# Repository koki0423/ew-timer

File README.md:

# timer

Arduino Nano を用いた 4 桁 7 セグメント表示付きタイマーの KiCad プロジェクトです。4 個の 4 ビット DIP スイッチで 16 ビットの設定値を入力し、開始/停止・リセット用の押しボタンで操作します。

このリポジトリには基板設計と製造データを収録しています。Arduino 用ファームウェア（`.ino` など）は含まれていません。

## 主な構成

| ブロック | 部品 | 役割 |
| --- | --- | --- |
| 制御 | A2: Arduino Nano v3.x | タイマー処理、表示走査、入力読取り |
| 表示 | U1: OSL-40391-LX | 4 桁・コモンカソードの 7 セグメント LED 表示器（コロン付き） |
| 表示駆動 | U2: 74HC595、R1-R8: 1 kΩ | シリアル出力を 8 本のセグメント信号（A-G、DP）へ展開。R1-R8 は各セグメントの電流制限抵抗 |
| 設定入力 | SW3-SW6: A7D-206-1、U3/U4: 74HC165、RN1-RN4: 10 kΩ | 4 個の 4 ビット DIP スイッチを 2 個の PISO シフトレジスタ経由で読み取る。各入力はプルダウンされ、スイッチ ON 時に High となる |
| 操作 | SW1、SW2 | リセット、開始/停止入力 |
| 状態表示 | U5: 74HC00、D1、R9: 300 Ω | DIP スイッチの一部を NAND 論理で判定し、エラー LED を点灯 |
| 電源安定化 | C1-C4: 0.1 µF | +5 V-GND 間のデカップリング |

基板外形は **120 mm × 90 mm**、板厚は **1.6 mm** です。表裏 2 層の配線を使用しています。

## Arduino Nano の接続

ファームウェアを作成する際は、以下の回路接続に合わせてピンを設定してください。

| Nano ピン | 接続先 | 用途 |
| --- | --- | --- |
| D2 | U2 SER (pin 14) | 7 セグメントのシリアルデータ |
| D3 | U2 RCLK (pin 12) | 74HC595 のラッチクロック |
| D4 | U2 SRCLK (pin 11) | 74HC595 のシフトクロック |
| D5 | U3/U4 `~PL` (pin 1) | DIP 入力のパラレルロード制御 |
| D6 | U3/U4 CP (pin 2) | DIP 入力のシフトクロック |
| D7 | U4 Q7 (pin 9) | 16 ビット DIP 入力のシリアル出力 |
| D9 | U1 DIG1 (pin 1) | 1 桁目の共通カソード選択 |
| D10 | U1 DIG2 (pin 2) | 2 桁目の共通カソード選択 |
| D11 | U1 DIG3 (pin 6) | 3 桁目の共通カソード選択 |
| D12 | U1 DIG4 (pin 8) | 4 桁目の共通カソード選択 |
| D13 | U1 COLON (pin 4) | コロン表示制御 |
| A0 | SW2 | 開始/停止ボタン。押下時は Low |
| A1 | SW1 | リセットボタン。押下時は Low |

U2 の出力は、`QA`-`QH` の順に `A`、`B`、`C`、`D`、`E`、`F`、`G`、`DP` セグメントへ接続されています。U3 の Q7 は U4 のシリアル入力へカスケード接続され、U4 の Q7 を Nano の D7 で読み取ります。

## 部品表

製造用の詳細 BOM は [production/bom.csv](production/bom.csv) を参照してください。主要部品は次のとおりです。

| 数量 | 部品 |
| ---: | --- |
| 1 | Arduino Nano v3.x |
| 1 | OSL-40391-LX 4 桁 7 セグメント LED 表示器 |
| 1 | 74HC595（DIP-16 ソケット） |
| 2 | 74HC165（DIP-16 ソケット） |
| 1 | 74HC00（DIP-14 ソケット） |
| 4 | A7D-206-1 4 ビット DIP スイッチ |
| 4 | 10 kΩ SIP 抵抗アレイ（5 ピン） |
| 8 | 1 kΩ 抵抗 |
| 1 | 300 Ω 抵抗 |
| 4 | 0.1 µF コンデンサ |
| 1 | 3 mm LED（エラー表示） |
| 2 | 12 mm タクトスイッチ |

## ファイル構成

| パス | 内容 |
| --- | --- |
| [timer.kicad_pro](timer.kicad_pro) | KiCad プロジェクト設定 |
| [timer.kicad_sch](timer.kicad_sch) | 回路図 |
| [timer.kicad_pcb](timer.kicad_pcb) | 基板レイアウト |
| [production/timer.zip](production/timer.zip) | 基板製造用 Gerber / ドリルデータ一式 |
| [production/bom.csv](production/bom.csv) | 製造・部品調達用 BOM |
| [production/positions.csv](production/positions.csv) | 部品実装座標 |
| [docs/](docs/) | 表示器、シフトレジスタ、DIP スイッチおよび LED ブラケットの資料 |

## 開き方と製造

1. KiCad で [timer.kicad_pro](timer.kicad_pro) を開きます。PCB ファイルは KiCad 10.0 形式です。
2. 回路図または基板を変更したら、ERC/DRC を実行してから製造データを再生成します。
3. 変更を加えず基板を発注する場合は、[production/timer.zip](production/timer.zip) を基板メーカーへアップロードします。
4. 実装には [production/bom.csv](production/bom.csv) と [production/positions.csv](production/positions.csv) を使用します。

## 注意事項

- `fp-lib-table` は A7D-206-1 用フットプリントについて、この PC 上の `C:/Users/koki/Downloads/...` を参照しています。このライブラリはリポジトリに含まれていないため、フットプリントを再割り当て・更新する場合は、同等のライブラリをローカルに追加して参照先を更新してください。
- U1 の回路図シンボルは OSL-40391-LX ですが、基板フットプリント名は `LTC-4627Jx` です。置換部品を選ぶ前に、同梱の [表示器データシート](docs/OSL40391-XX.pdf) でピン配列・極性・寸法を必ず照合してください。
- Nano の +5 V を基板全体の電源として使用します。USB 給電以外を用いる場合も、ロジック電源は +5 V、GND 共通にしてください。
- 7 セグメント表示は Nano による桁走査を想定しています。表示の極性、桁選択のタイミング、DIP スイッチのビット順は、実機で確認しながらファームウェア側で定義してください。

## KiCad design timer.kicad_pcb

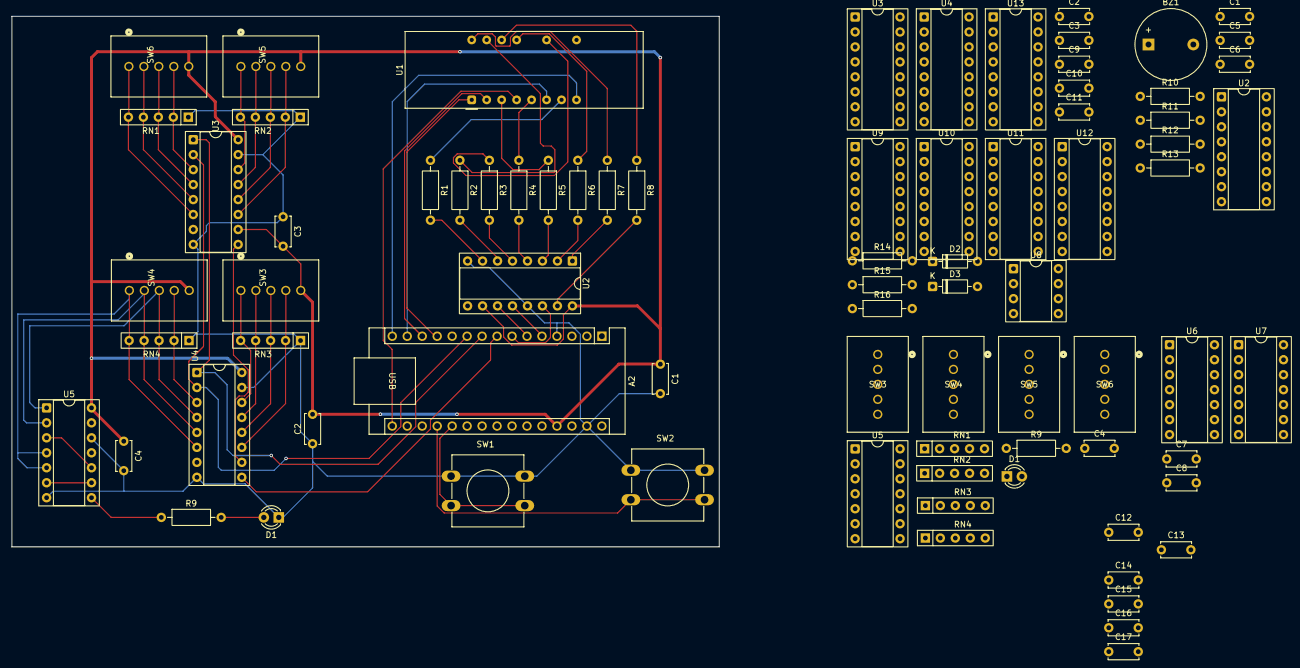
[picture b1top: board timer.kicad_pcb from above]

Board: 2 copper layers, 120.0 x 90.0 mm, 79 parts (0 on the bottom side), 110 nets.

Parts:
A2: Arduino_Nano_R4; Arduino_Nano
BZ1: Buzzer; Buzzer_12x9.5RM7.6
C1, C2, C3, C4#2, C7, C8, C12, C13, C14, C15, C16, C17: 0.1u; C_Disc_D5.0mm_W2.5mm_P5.00mm
C1#2, C2#2, C3#2, C4: 0.1μF; C_Disc_D5.0mm_W2.5mm_P5.00mm
C5, C6: 1u; C_Disc_D5.0mm_W2.5mm_P5.00mm
C9: 4.7u; C_Disc_D5.0mm_W2.5mm_P5.00mm
C10: 0.01u; C_Disc_D5.0mm_W2.5mm_P5.00mm
C11: 10n; C_Disc_D5.0mm_W2.5mm_P5.00mm
D1, D1#2: error_LED; LED_D3.0mm
D2, D3: 1SS106; D_DO-35_SOD27_P7.62mm_Horizontal
R1, R2, R3, R4, R5, R6, R7, R8, R16: 1k; R_Axial_DIN0207_L6.3mm_D2.5mm_P10.16mm_Horizontal
R9, R9#2: 300; R_Axial_DIN0207_L6.3mm_D2.5mm_P10.16mm_Horizontal
R10, R11, R12, R13: 10k; R_Axial_DIN0207_L6.3mm_D2.5mm_P10.16mm_Horizontal
R14, R15: 100k; R_Axial_DIN0207_L6.3mm_D2.5mm_P10.16mm_Horizontal
RN1, RN1#2, RN2, RN2#2, RN3, RN3#2, RN4, RN4#2: 10k; R_Array_SIP5
SW1: reset_btn; SW_PUSH-12mm
SW2: start_stop_btn; SW_PUSH-12mm
SW3, SW3#2, SW4, SW4#2, SW5, SW5#2, SW6, SW6#2: A7D-206-1; A7D-206-1_OMR
U1: OSL-40391-LX; LTC-4627Jx
U2, U2#2: 74HC595; DIP-16_W7.62mm_Socket
U3, U3#2, U4, U4#2: 74HC165; DIP-16_W7.62mm_Socket
U5, U5#2: 74HC00; DIP-14_W7.62mm_Socket
U6: 74HC14; DIP-14_W7.62mm_Socket
U7: 74HC74; DIP-14_W7.62mm_Socket
U8: NE555D; DIP-8_W7.62mm_Socket
U9, U10, U11, U12: 74HC192; DIP-16_W7.62mm_Socket
U13: 74HC157; DIP-16_W7.62mm_Socket

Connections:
/1Hz発振回路/HC14-in: C11.2, R16.1, U6.13
/1Hz発振回路/HC14-out: D2.2 (A), U6.6
/1Hz発振回路/QA-D0-m: U3.11 (D0), U10.3 (QA)
/1Hz発振回路/QA-D0-s: U4#2.11 (D0), U12.3 (QA)
/1Hz発振回路/QA-D4-m: U3.3 (D4), U9.3 (QA)
/1Hz発振回路/QA-D4-s: U4#2.3 (D4), U11.3 (QA)
/1Hz発振回路/QB-D1-m: U3.12 (D1), U10.2 (QB)
/1Hz発振回路/QB-D1-s: U4#2.12 (D1), U12.2 (QB)
/1Hz発振回路/QB-D5-m: U3.4 (D5), U9.2 (QB)
/1Hz発振回路/QB-D5-s: U4#2.4 (D5), U11.2 (QB)
/1Hz発振回路/QC-D2-m: U3.13 (D2), U10.6 (QC)
/1Hz発振回路/QC-D2-s: U4#2.13 (D2), U12.6 (QC)
/1Hz発振回路/QC-D6-m: U3.5 (D6), U9.6 (QC)
/1Hz発振回路/QC-D6-s: U4#2.5 (D6), U11.6 (QC)
/1Hz発振回路/QD-D3-m: U3.14 (D3), U10.7 (QD)
/1Hz発振回路/QD-D3-s: U4#2.14 (D3), U12.7 (QD)
/1Hz発振回路/QD-D7-m: U3.6 (D7), U9.7 (QD)
/1Hz発振回路/QD-D7-s: U4#2.6 (D7), U11.7 (QD)
/1Hz発振回路/clk_out: U8.3 (OUT), U12.4 (DOWN)
/A1: A2.20 (A1), U7.5 (Q)
/CP: A2.10 (D7), U3.2 (CP), U4#2.2 (CP)
/D2: A2.5 (D2), U2#2.12 (RCLK)
/D3: A2.6 (D3), U2#2.11 (SRCLK)
/D4: A2.7 (D4), U2#2.14 (SER)
/D5: A2.8 (D5), U4#2.9 (Q7)
/D8: A2.11 (D8), R9.1, U5.8
/PL: A2.9 (D6), U3.1 (~PL), U4#2.1 (~PL)
/VCC: A2.27 (+5V), C1.1, C2.2, C3.2, C4#2.1, C7.2, C8.1, C12.2, C13.2, C14.2, C15.2, C16.1, C17.2, R10.1, R12.1, R15.1, SW3.C, SW4.C, SW5.C, SW6#2.C, U2#2.16 (VCC), U3.10 (DS), U3.16 (VCC), U4#2.16 (VCC), U5.14 (VCC), U6.14 (VCC), U7.4 (~S), U7.10 (~S), U7.14 (VCC), U8.8 (VCC), U9.5 (UP), U9.16 (VCC), U10.5 (UP), U10.16 (VCC), U11.5 (UP), U11.16 (VCC), U12.5 (UP), U12.16 (VCC), U13.2 (1A), U13.11 (3A), U13.16 (VCC)
GND: A2.4 (GND), A2.29 (GND), BZ1.2 (-), C1.2, C1#2.2, C2.1, C2#2.1, C3.1, C3#2.1, C4.2, C4#2.2, C5.1, C6.1, C7.1, C8.2, C9.1, C10.2, C11.1, C12.1, C13.1, C14.1, C15.1, C16.2, C17.1, D1.1 (K), D1#2.1 (K), RN1.1 (common), RN1#2.1 (common), RN2.1 (common), RN2#2.1 (common), RN3.1 (common), RN3#2.1 (common), RN4.1 (common), RN4#2.1 (common), SW1.1, SW2.1, U2.8 (GND), U2.13 (~OE), U2#2.8 (GND), U2#2.13 (~OE), U3.8 (GND), U3.15 (~CE), U3#2.8 (GND), U3#2.15 (~CE), U4.8 (GND), U4.15 (~CE), U4#2.8 (GND), U4#2.15 (~CE), U5.7 (GND), U5.12, U5.13, U5#2.7 (GND), U5#2.12, U5#2.13, U6.7 (GND), U6.9, U6.11, U7.7 (GND), U7.11 (C), U7.13 (~R), U8.1 (GND), U9.8 (GND), U9.14 (CLR), U10.8 (GND), U10.14 (CLR), U11.8 (GND), U11.14 (CLR), U12.8 (GND), U12.14 (CLR), U13.5 (2A), U13.8 (GND), U13.14 (4A), U13.15 (~ST)
unnamed: C1#2.1, C2#2.2, C3#2.2, C4.1, SW3#2.C, SW4#2.C, SW5#2.C, SW6.C, U2.10 (~SRCLR), U2.16 (VCC), U3#2.10 (DS), U3#2.16 (VCC), U4.16 (VCC), U5#2.14 (VCC)
unnamed: A2.26 (A7), BZ1.1 (+)
unnamed: U3#2.1 (~PL), U4.1 (~PL)
unnamed: U3#2.2 (CP), U4.2 (CP)
unnamed: A2.12 (D9), U1.1 (DIG1)
unnamed: A2.13 (D10), U1.2 (DIG2)
unnamed: A2.14 (D11), U1.6 (DIG3)
unnamed: A2.15 (D12), U1.8 (DIG4)
unnamed: A2.16 (D13), U1.4 (COLON)
unnamed: D1.2 (A), D1#2.2 (A), R9.2, R9#2.2
unnamed: D2.1 (K), D3.1 (K), U11.11 (~LOAD)
unnamed: R9#2.1, U5#2.8
unnamed: R10.2, R11.1, SW2.2
unnamed: R12.2, R13.1, SW1.2
unnamed: RN1.2 (R1), SW6.1, U3#2.3 (D4)
unnamed: RN1.3 (R2), SW6.2, U3#2.4 (D5)
unnamed: RN1.4 (R3), SW6.4, U3#2.5 (D6)
unnamed: RN1.5 (R4), SW6.8, U3#2.6 (D7)
unnamed: RN2.2 (R1), SW5#2.1, U3#2.11 (D0)
unnamed: RN2.3 (R2), SW5#2.2, U3#2.12 (D1)
unnamed: RN2.4 (R3), SW5#2.4, U3#2.13 (D2)
unnamed: RN2.5 (R4), SW5#2.8, U3#2.14 (D3)
unnamed: RN3.2 (R1), SW3#2.1, U4.11 (D0)
unnamed: RN3.3 (R2), SW3#2.2, U4.12 (D1)
unnamed: RN3.4 (R3), SW3#2.4, U4.13 (D2)
unnamed: RN3.5 (R4), SW3#2.8, U4.14 (D3)
unnamed: RN4.2 (R1), SW4#2.1, U4.3 (D4)
unnamed: RN4.3 (R2), SW4#2.2, U4.4 (D5), U5#2.1
unnamed: RN4.4 (R3), SW4#2.4, U4.5 (D6), U5#2.2
unnamed: RN4.5 (R4), SW4#2.8, U4.6 (D7), U5#2.4, U5#2.5
unnamed: R8.1, U1.14 (A)
unnamed: R7.1, U1.16 (B)
unnamed: R6.1, U1.13 (C)
unnamed: R5.1, U1.3 (D)
unnamed: R1.1, U1.7 (DP)
unnamed: R4.1, U1.5 (E)
unnamed: R3.1, U1.11 (F)
unnamed: R2.1, U1.15 (G)
unnamed: R8.2, U2.15 (QA), U2#2.15 (QA)
unnamed: R7.2, U2.1 (QB), U2#2.1 (QB)
unnamed: R6.2, U2.2 (QC), U2#2.2 (QC)
unnamed: R5.2, U2.3 (QD), U2#2.3 (QD)
unnamed: R4.2, U2.4 (QE), U2#2.4 (QE)
unnamed: R3.2, U2.5 (QF), U2#2.5 (QF)
unnamed: R2.2, U2.6 (QG), U2#2.6 (QG)
unnamed: R1.2, U2.7 (QH), U2#2.7 (QH)
unnamed: U3.9 (Q7), U3#2.9 (Q7), U4.10 (DS), U4#2.10 (DS)
unnamed: U5.6, U5.9, U5#2.6, U5#2.9
unnamed: U5.3, U5.10, U5#2.3, U5#2.10
unnamed: U6.5, U6.12
unnamed: U6.2, U7.3 (C)
unnamed: U7.2 (D), U7.6 (~Q)
unnamed: U6.4, U7.1 (~R)
unnamed: C10.1, U8.5 (CONT)
unnamed: R14.1, R15.2, U8.7 (DISCH)
unnamed: C9.2, R14.2, U8.2 (TRIG), U8.6 (THRES)
unnamed: R16.2, U10.4 (DOWN), U11.13 (~BO)
unnamed: U9.4 (DOWN), U10.13 (~BO)
unnamed: U11.15 (A), U13.4 (1Y)
unnamed: U11.1 (B), U13.7 (2Y)
unnamed: U11.10 (C), U13.9 (3Y)
unnamed: U11.9 (D), U13.12 (4Y)
unnamed: U11.4 (DOWN), U12.13 (~BO), U13.1 (SELECT)
SW3_1: RN3#2.2 (R1), SW3.1, U12.15 (A)
SW3_2: RN3#2.3 (R2), SW3.2, U12.1 (B)
SW3_4: RN3#2.4 (R3), SW3.4, U12.10 (C)
SW3_8: RN3#2.5 (R4), SW3.8, U12.9 (D)
SW4_1: RN4#2.2 (R1), SW4.1, U13.3 (1B)
SW4_2: RN4#2.3 (R2), SW4.2, U5.1, U13.6 (2B)
SW4_4: RN4#2.4 (R3), SW4.4, U5.2, U13.10 (3B)
SW4_8: RN4#2.5 (R4), SW4.8, U5.4, U5.5, U13.13 (4B)
SW5_1: RN2#2.2 (R1), SW5.1, U10.15 (A)
SW5_2: RN2#2.3 (R2), SW5.2, U10.1 (B)
SW5_4: RN2#2.4 (R3), SW5.4, U10.10 (C)
SW5_8: RN2#2.5 (R4), SW5.8, U10.9 (D)
SW6_1: RN1#2.2 (R1), SW6#2.1, U9.15 (A)
SW6_2: RN1#2.3 (R2), SW6#2.2, U9.1 (B)
SW6_4: RN1#2.4 (R3), SW6#2.4, U9.10 (C)
SW6_8: RN1#2.5 (R4), SW6#2.8, U9.9 (D)
reset_btn: C6.2, D3.2 (A), R13.2, U6.3, U9.11 (~LOAD), U10.11 (~LOAD), U12.11 (~LOAD)
start-stop_btn: C5.2, R11.2, U6.1, U8.4 (~RST)

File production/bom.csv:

Designator,Footprint,Quantity,Value,LCSC Part #
A2,Arduino_Nano,1,Arduino_Nano_v3.x,
"C1, C2, C3, C4",C_Disc_D5.0mm_W2.5mm_P5.00mm,4,0.1μF,
D1,LED_D3.0mm,1,error_LED,
"R1, R2, R3, R4, R5, R6, R7, R8",R_Axial_DIN0207_L6.3mm_D2.5mm_P10.16mm_Horizontal,8,1k,
R9,R_Axial_DIN0207_L6.3mm_D2.5mm_P10.16mm_Horizontal,1,300,
"RN1, RN2, RN3, RN4",R_Array_SIP5,4,10k,
SW1,SW_PUSH-12mm,1,reset_btn,
SW2,SW_PUSH-12mm,1,start_stop_btn,
"SW3, SW4, SW5, SW6",A7D-206-1_OMR,4,A7D-206-1,
U1,LTC-4627Jx,1,OSL-40391-LX,
U2,DIP-16_W7.62mm_Socket,1,74HC595,
"U3, U4",DIP-16_W7.62mm_Socket,2,74HC165,
U5,DIP-14_W7.62mm_Socket,1,74HC00,
